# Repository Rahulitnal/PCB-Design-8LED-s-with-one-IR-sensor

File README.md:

# PCB-Design-8LED-s-with-one-IR-sensor
PCB design using KiCad which is having 8 leds and one IR sensor and on pullup resister

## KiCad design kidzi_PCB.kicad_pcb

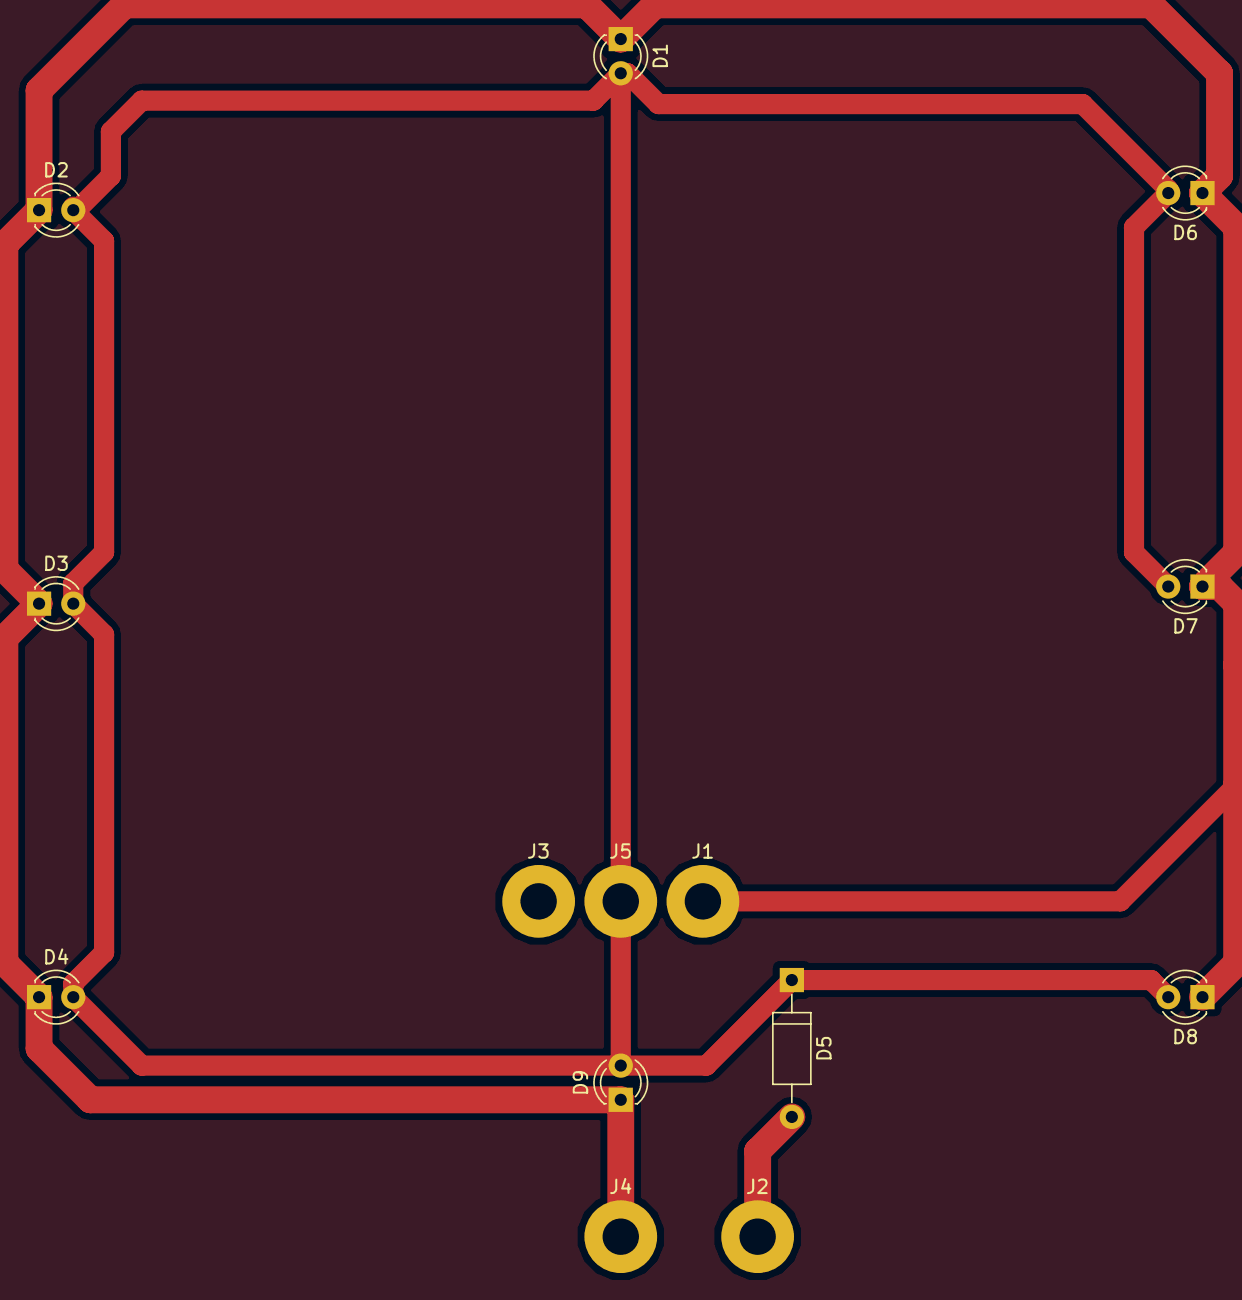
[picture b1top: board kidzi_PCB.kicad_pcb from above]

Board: 2 copper layers, 14 parts (0 on the bottom side), 3 nets.

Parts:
D1, D2, D3, D4, D6, D7, D8, D9: LED; LED_D3.0mm
D5: D; D_A-405_P10.16mm_Horizontal
J1, J4: GND; MountingHole_2.7mm_M2.5_Pad
J2, J5: Vcc; MountingHole_2.7mm_M2.5_Pad
J3: D0; MountingHole_2.7mm_M2.5_Pad

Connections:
unnamed: D1.1, D2.1, D3.1, D4.1, D6.1, D7.1, D8.1, D9.1, J1.1, J4.1
unnamed: D1.2, D2.2, D3.2, D4.2, D5.1, D6.2, D7.2, D8.2, D9.2, J5.1
unnamed: D5.2, J2.1
